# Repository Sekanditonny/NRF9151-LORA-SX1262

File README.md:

## 1. Overview

This design is a production-optimized modification of the open-source nRF9151 Feather platform, tailored for animal tracking applications.

The system integrates:

- Cellular (NTN/LTE-M/NB-IoT) + GPS via nRF9151
- LoRa communication# Animal Tracker PCB — nRF9151 + SX1262
 via SX1262
- Dual battery support (LiPo + Solar OR LiSOCl₂)
- Ultra-low power operation
- Compact form factor (≤ 50.8mm × 22.86mm)

All development-board-specific and non-essential components have been removed to improve cost, efficiency, and manufacturability.

---

## 2. Removed Components

The following features from the original Feather design are excluded:

- RP2040 co-processor
- USB-C interface
- External NOR Flash (Winbond 4MB)
- Non-essential push buttons (only Reset retained)
- QWIIC connector

---

## 3. Core Functional Blocks

### 3.1 Main Processing Unit

**nRF9151 SiP**

- Integrated LTE-M / NB-IoT / NTN modem
- Integrated GPS
- Main MCU for system control
- Interfaces with LoRa module and power control logic

### 3.2 LoRa Communication

**SX1262** (SMD 16×16mm module)

- SPI-connected to nRF9151
- Controlled via GPIO (including power gating)
- External U.FL antenna connector
- Internal RF matching (no external matching network required)
- Optimized for low-cost (~$2.8) and long-range communication

---

## 4. Power Architecture

### 4.1 Dual Battery Support

The system supports two mutually exclusive power configurations:

**LiPo Battery (Rechargeable)**
- Charged via solar input
- Managed by CN3165 solar charge controller

**LiSOCl₂ Battery (Primary)**
- Non-rechargeable
- Used for ultra-long-life deployments

### 4.2 Power Path Management

**LTC4412 Ideal Diode Controller**

- Automatically selects active power source
- Prevents reverse current
- Ensures seamless switching between battery types

### 4.3 Voltage Regulation Strategy

Instead of a PMIC (e.g., nPM1300), the design uses:

- Two buck regulators (Master + Slave)
- Controlled using RC timing + PGOOD logic
- Eliminates need for external microcontroller for sequencing

---

## 5. Power Sequencing (Critical Design)

The system uses RC-based timing ("power inertia") to meet nRF9151 strict requirements:

- VDD (core) must power ON first and OFF last
- VDD_GPIO must power OFF first

### 5.1 Master Rail (Main 3.3V – Core Supply)

**Components:**
- 100kΩ resistor
- 10µF capacitor

**Behavior:**
- Startup delay: ~700ms
- Shutdown delay: ~1000ms

**Purpose:**
- Provides stable core voltage
- Allows LTE modem network detach, safe flash memory writes, and system state preservation

### 5.2 Slave Rail (GPIO Supply – Fast Rail)

**Components:**
- 100kΩ pull-down
- 10nF capacitor

**Behavior:**
- Startup: activates after master reaches ~95%
- Shutdown: discharges in ~1ms

**Purpose:**
- Ensures GPIO power drops before core power
- Prevents back-powering through I/O pins

---

## 6. Solar Charging System

**CN3165 Solar Charge Controller**

- Handles LiPo charging from solar panel
- Efficient energy harvesting
- Supports autonomous field deployment
- Protects nRF9151 integrity

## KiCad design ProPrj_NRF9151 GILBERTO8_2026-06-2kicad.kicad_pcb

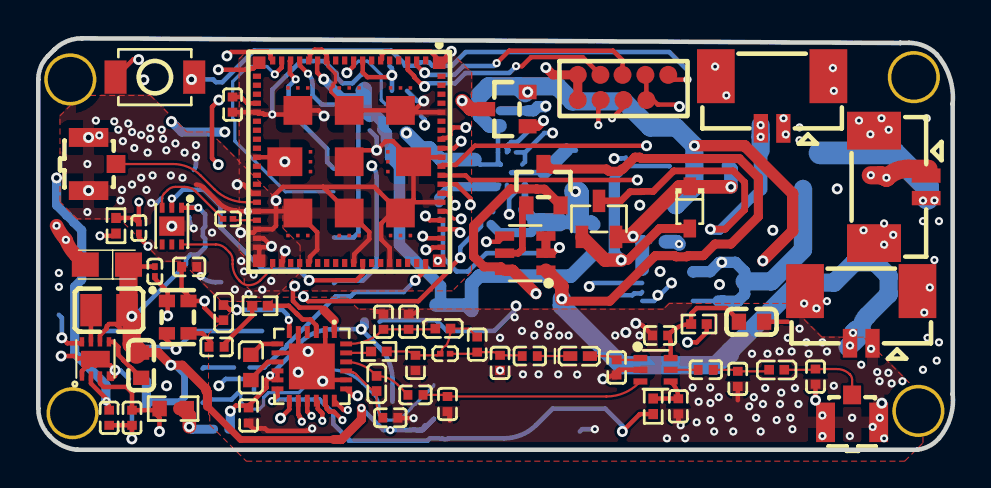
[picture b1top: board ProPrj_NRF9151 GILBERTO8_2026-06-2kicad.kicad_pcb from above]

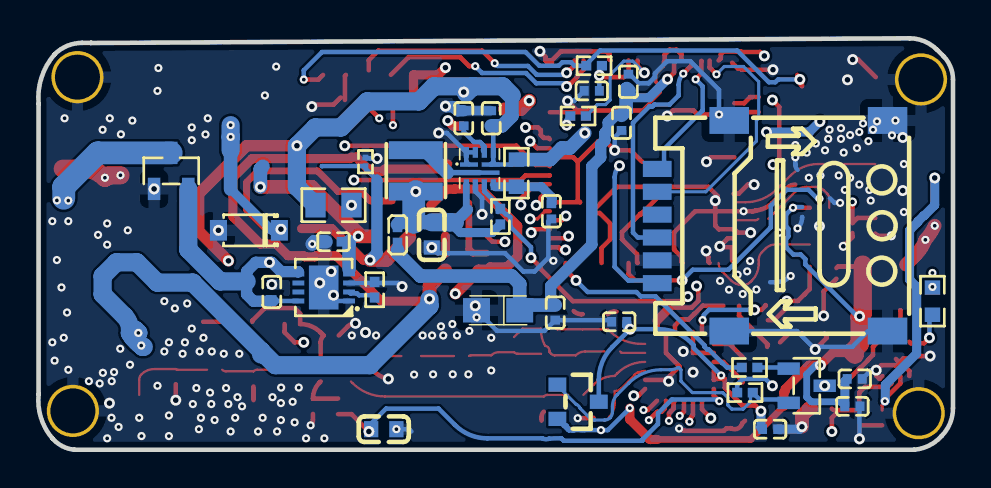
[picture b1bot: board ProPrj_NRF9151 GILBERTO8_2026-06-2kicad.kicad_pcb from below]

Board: 4 copper layers, 50.8 x 22.9 mm, 94 parts (35 on the bottom side), 72 nets.

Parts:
C3, C7, C12, C13, C17, C18, C41, C42, C43, C44, C45, C46, C47, C48, C49, C56, C57, C76, C81, C83, C85, C88, C89, C90, C91, C92, C93, C94, C95, C96, C97, C98, C99, C100: C0402
C14, C15, C101, C102: C0603
C50, C51: CASE-A_3216
C52, C53, C54: C0201
CARD2: SIM-SMD_SIM-1305-6P
CN4, CN5, CN6: CONN-SMD_2P-P1.25_A1251WV-S-2P
D5: SOD-123_L2.8-W1.8-LS3.7-RD
D6: SOD-323_L1.8-W1.3-LS2.5-RD
L3: IND-SMD_L3.0-W3.0_SWPA3010S
L4: L0806
L20, L23, L24, L26, L27: L0402
L21: L0201
L22: L0402-R-RD
Q1, Q2, Q3: SOT-23_L2.9-W1.3-P1.90-LS2.4-BR
Q6, Q7, Q8: SOT-23-3_L2.9-W1.3-P1.90-LS2.4-BR
R8, R9, R13: R0603
R11, R47, R49, R50, R51, R52, R53, R57, R58, R59, R60: R0402
R46: R0201
R48: R0805
RF2, RF3: RF-SMD_FRF05002-JSS103M
SW2: SW-SMD_L3.9-W3.0-P4.45
U1: LGA-113_L12.1-W11.1_NRF9151-LACA-R7
U5: SOT-23-6_L2.9-W1.6-P0.95-LS2.8-BL
U8: MCM-6_L2.3-W1.7-P0.54-TL-EP
U9: VQFN-11_L2.0-W2.0-P0.50-TL_TI_RWK
U10: WSON-8_L2.0-W2.0-P0.50-TL-EP
U11: DFN-8_L3.0-W3.0-P0.50-BL-EP
U13: QFN-24_L4.0-W4.0-P0.50-BL-EP2.6
U14: SC-70-6_L2.2-W1.3-P0.65-LS2.1-BL
U15: L0603
U16: J CONNEXCO
X1: OSC-SMD_4P-L2.0-W1.6-BL_1XXD

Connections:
3.3V_SYS_2A: C14.2, L3.2, L27.2, R11.1, R50.2, R53.1, U9.3, U16.1, U16.6
$1N5599: C12.2, U9.9
$1N5840: L3.1, U9.2
$1N6280: C15.2, U10.5
$1N6332: R8.2, U10.8
$1N6408: L4.2, U10.7
$1N6706: C18.2, R9.1, U9.6
$1N7225: CN4.2, Q8.3
$1N7651: CN5.2, D5.1, Q6.3
$1N7654: D6.2, Q6.1, R46.1
$1N7658: R47.2, U11.2
$1N7845: CN6.2, Q1.3, U5.1
$1N7884: Q1.1, U5.5
$1N7906: Q2.1, R48.1, U5.4
$1N8450: Q7.1, R49.2
$1N10304: Q3.1, Q7.2, R50.1
$1N10488: C44.2, R51.2, U1.9
$1N10935: C45.2, U1.24
$1N12604: C52.1, U8.3
$1N15358: R57.2, U13.3
$1N15364: C88.2, R57.1
$1N15368: C88.1, X1.3
$1N15674: U13.7, U15.2
$1N15679: U13.9, U15.1
$1N16005: R58.1, U13.23
$1N16052: C90.2, C91.2, L20.2, U13.24
$1N16301: C76.2, C92.1, L20.1, L21.1, R58.2
$1N16358: C92.2, C93.2, C94.1, L21.2
$1N16409: C94.2, L22.1
$1N16412: C95.2, L22.2, U14.1
$1N16561: C96.2, L23.1, U13.21
$1N16740: C81.2, C97.2, U14.3
$1N16747: C97.1, L23.2, U13.22
$1N17013: C85.2, C102.2, R59.2, U14.6
$1N17155: C98.1, U14.5
$1N17206: C98.2, C99.2, L24.1
$1N17209: C100.2, L24.2, RF3.1
$1N17526: C56.1, L26.1, X1.4
$1N35658: C83.2, R60.2, U14.4
ANT_SW: R59.1, U1.73
BUSY: U1.68, U13.14
COEX0: C53.1, R52.1, U1.52, U8.2
DEB_RX: U1.69, U16.7
DEB_TX: U1.70, U16.8
DI01: U1.72, U13.13
DI03: L26.2, U13.6
DIO2: C101.1, R60.1, U13.12
ENABLE: R53.2, U1.10
ENABLE_3.3VGPIO: C17.2, R11.2, R13.1, U9.5, U10.3
GND: C3.1, C7.1, C12.1, C13.1, C14.1, C17.1, C18.1, C41.1, C42.1, C43.2, C44.1, C45.1, C46.2, C47.2, C48.1, C49.1, C50.2, C51.2, C53.2, C54.2, C56.2, C57.2, C76.1, C81.1, C83.1, C85.1, C89.1, C90.1, C91.1, C93.1, C95.1, C96.1, C99.1, C100.1, C101.2, C102.1, CARD2.7, CARD2.8, CARD2.9, CARD2.10, CARD2.C5, CN4.1, CN4.3, CN4.4, CN5.1, CN5.3, CN5.4, CN6.1, CN6.3, CN6.4, D5.2, Q7.3, Q8.1, R13.2, R46.2, R47.1, R52.2, RF2.2, RF2.3, RF3.2, RF3.3, SW2.2, U1.1, U1.7, U1.13, U1.15, U1.20, U1.25, U1.30, U1.34, U1.36, U1.38, U1.39, U1.40, U1.41, U1.43, U1.46, U1.51, U1.55, U1.60, U1.66, U1.71, U1.76, U1.105, U1.106, U1.107, U1.108, U1.109, U1.110, U1.111, U1.112, U1.113, U5.2, U5.3, U8.7, U9.1, U9.4, U9.10, U9.11, U10.1, U10.4, U10.9, U11.1, U11.3, U11.9, U13.2, U13.5, U13.8, U13.20, U13.25, U14.2, U16.4, U16.9, X1.1, X1.2
GPIO3V3_LORA_500MA: C15.1, C47.1, C48.2, C51.1, C54.1, L4.1, Q3.2, R8.1, U1.65, U8.1, U10.6
LORA_VOLTAGE_ENABLE: R49.1, U1.59
MISO: U1.62, U13.16
MOSI: U1.64, U13.17
NRESET: U1.67, U13.15
NRF9151-VDD: C3.2, C46.1, C49.2, C50.1, L27.1, U1.14
NSS: U1.61, U13.19
RESET: R51.1, SW2.1, U16.5
RF_ANT: RF2.1, U1.35
RF_AUX: C52.2, U1.37
RF_GPS: U1.42, U8.6
SCK: U1.63, U13.18
SIM_CLK: CARD2.C3, U1.18
SIM_IO: CARD2.C7, U1.17
SIM_RST: CARD2.C2, U1.16
SIM_VCC: CARD2.C1, U1.19
SOLAR_PV: C41.2, D6.1, Q6.2, U11.4
SWDCLK: U1.3, U16.3
SWDIO: U1.4, U16.2
VBAT: C42.2, Q2.3, Q8.2, U11.5, U11.8
VDD_SX126: C43.1, C57.1, C89.2, Q3.3, U13.1, U13.10, U13.11
VIN: C7.2, C13.2, Q1.2, Q2.2, R9.2, R48.2, U5.6, U9.7, U9.8, U10.2

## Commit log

2026-06-28 Enhance README with detailed module specifications
    Expanded the README to provide detailed information about the NRF9151-LORA-SX1262 animal tracker module, including an overview, removed components, core functional blocks, power architecture, power s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
